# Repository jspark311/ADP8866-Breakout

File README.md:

# ADP8866-Breakout

A breakout board for Analog Devices' ADP8866 LED PMIC.

#### [Hackaday.io Page](https://hackaday.io/project/167233-adp8866-breakout)

#### [Order from Tindie](https://www.tindie.com/products/17866/)

------------------------

### What is in this repository:

**./doc**:  Location for documentation

**./KiCAD**:  Hardware design files

**./Arduino**:  Arduino driver

------------------------

Front | Back
:-------:|:------:
 |

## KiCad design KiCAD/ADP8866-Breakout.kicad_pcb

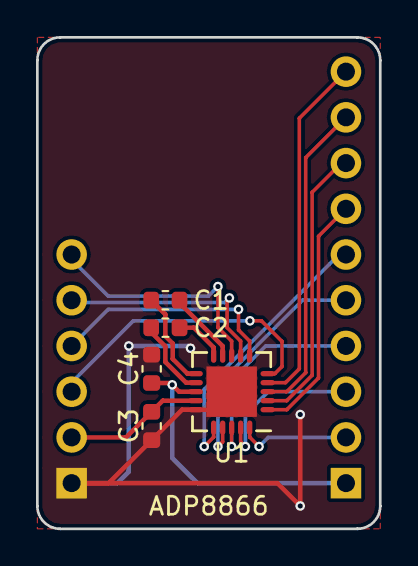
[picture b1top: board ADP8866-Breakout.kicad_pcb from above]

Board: 2 copper layers, 19.1 x 27.3 mm, 7 parts (0 on the bottom side), 20 nets.

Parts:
C1, C2, C3, C4: 1uF; C_0603_1608Metric
J1: Conn_01x06; PinHeader_1x06_P2.54mm_Vertical
J2: Conn_01x10; PinHeader_1x10_P2.54mm_Vertical
U1: ADP8866; UQFN-20-1EP_4x4mm_P0.5mm_EP2.8x2.8mm

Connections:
/D1: J2.9, U1.3
/D2: J2.8, U1.2
/D3: J2.7, U1.1
/D4: J2.2, U1.20
/D5: J2.3, U1.19
/D6: J2.4, U1.18
/D7: J2.5, U1.17
/D8: J2.6, U1.16
/D9: J2.10, U1.4
/GND: C3.1, C4.1, J1.1, U1.0, U1.15
/Vcc: C3.2, J1.2, U1.14
unnamed: C1.1, U1.11
unnamed: C1.2, U1.9
unnamed: C2.1, U1.10
unnamed: C2.2, U1.12
unnamed: C4.2, J2.1, U1.13
unnamed: J1.3, U1.5
unnamed: J1.4, U1.6
unnamed: J1.5, U1.7
unnamed: J1.6, U1.8

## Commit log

2019-05-13 Adding Osh renders and doc.
2019-08-21 Adding hardware, and updating README.
2019-08-21 One day, I will remember all the rules the first time.
2019-08-21 Updating README.
2019-08-21 Adding arduino boilerplate and an unported driver.
2019-08-21 Minor naming fix.
2019-08-21 Minor Removing duplicate files.
